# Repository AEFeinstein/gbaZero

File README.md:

View this project on [CADLAB.io](https://cadlab.io/project/1072). 

# gbaZero

One day I decided to buy a broken Gameboy Advance, gut it, and replace the innards with a Raspberry Pi powered board. This style of project has been attempted before in custom plastic (see [Game Grrl](https://learn.adafruit.com/game-grrl) and its derivitaves) and Nintendo plastic (see [Ryzee119's project](https://github.com/Ryzee119/GBA_Emulator-by-Ryzee119-) and [Game Pie Advance](http://gamepieadvance.com/)). Here's a little build log for my version of this project.

## Design

The design process was mostly me sitting at my desk doing research and CAD work in Inkscape and EAGLE.

To get the right PCB shape, I desoldered all the parts from a sacrificial PCB and took a 600dpi scan of it.

That scan was then traced in Inkscape, and the resulting SVG was imported into EAGLE using [cmonr's svg2poly ULP](https://github.com/cmonr/Eagle-ULPs).

I wanted the wacky button footprints to be just like Nintendo's. I had a scan of the footprints open in an image viewer, overlaid an EAGLE window made transparent by [Peek Through](http://www.lukepaynesoftware.com/projects/peek-through/), and traced out the shape using the polygon tool. It's kind of like a high tech lightbox.

Ultimately I threw my work on the board shape and drilled holes out the window in favor of the shape from Ryzee119's project. I was almost guaranteed to mess something, and their's was already tested to be the right fit, so that seemed safer. I was also unaware of Ryzee119's project when I started all the scanning and tracing. I did keep the Nintendo-esque button footprints.

## Assembling the Hardware

### Power Circuitry

It turns out using someone else's work is often easier than doing it yourself. In this case, I used a [PowerBoost 1000C](https://www.adafruit.com/products/2465) to manage charging the battery and supplying power for this board. It's a capable little board, so all I had to do was desolder the JST battery connector to trim the height and cover the backside with electrical tape because it will sit flush on the main board.

Here's the power circuit all soldered up. I'm using a common anode tricolor LED and some NOR gates and inverters to display the GBA's state (powered on, charging, or low battery). The logic ICs are in the top left and the LED is on the other side of the board.

The switch in the bottom right was salvaged from a broken GBA. I couldn't find where to source a replacement for the life of me. The resistor and diode in the bottom right are a way to have the Raspberry Pi power off cleanly. Sure, one could just cut power to the Pi, but that puts the SD card at risk for corruption. The Enable pin on the PowerBoost is tied to both the switch and a GPIO (through a diode, so the GPIO doesn't get backpowered), so when the Pi boots it holds the PowerBoost on, even if the switch is turned off. Flicking the switch off does trigger a shutdown script, which shuts down cleanly and disables the PowerBoost at the end.

Uhoh, notice those ugly wires coming off the logic ICs in the previous image? Turns out I either used the wrong footprint in EAGLE or ordered the wrong package part from Digi-Key. Either way, it needed some bridging. I realized I could take pictures with my phone through the stereo microscope in the lab, so I did. I trimmed the wires after this shot, and cleaned up the extra flux too.

There's nothing like a little hot glue to keep everything in place!

Ta-da! The LED works and is in the right place for the light pipe. It may be a little too bright, but that's nothing a larger current limiting resistor can't fix. The LED is blue when the unit is powered on, green when it is charging, and red when the battery is low. The one wrinkle is that the LED is off when the unit is off, but charging. The original design assumed a common cathode LED instead of a common anode LED, which is what I ended up finding on Digi-Key. Rather than redo the logic, I just threw an inverter on at the end. Unfortunately the inverter was powered by the regulated voltage, so it doesn't invert unless the unit is on. Had the LED been common cathode, it would have been driven by the 5V USB charging voltage. Ah well.

Also of note, the board uses the original Link Cable connector and a custom cable for charging. The Raspberry Pi's RX and TX pins are also exposed on the Link Cable connector, so with an FTDI cable one can log into a terminal and fiddle around with the system. This ended up being way more convenient than SSHing into the system over wifi.

### Display Circuitry

Remember that part about using someone else's work? I'll call it standing on the shoulders of giants. Turns out Adafruit sells a [2.8" Raspberry Pi display](https://www.adafruit.com/products/2423) which fits pretty perfectly in a GBA. I took the [circuitry from their board](https://github.com/adafruit/Adafruit-PiTFT-Plus-2.8-PCB) and transposed it onto mine. Should work perfectly, right? Yeah, we'll get to that.

Here's a gratuitious microscope shot. The display connector had 0.5mm pitch pins, which is the smallest thing I've soldered. Solder braid makes everything look super clean (and not bridged).

Oh yeah, I was going wild with that microscope. There's actually a problem in this picture. I'll get to that shortly.

Transposing a circuit only works if you do it correctly, which I did not. I crossed the I2C lines which send touchscreen data to the Raspberry Pi, so I had to cut those traces with a knife and reroute them with magnet wire. Those are the two wires going off the edge of the board. That didn't matter so much as I wasn't using the touchscreen anyway, but I like to be proper. The bigger issue is that I completely missed a trace that had been connected with a 0 ohm resistor on Adafruit's board. That was fixed with the third magnet wire running from the display connector to U1. I opted for kapton tape instead of hot glue to hold these fixes in place.

There was another issue with the display circuitry that prevented an image from being displayed, hinted at before. U1 is an APX803 voltage supervisor on a 3.3V line. However, I bought an APX803 which had a 4.63V threshold. D'oh. The Adafruit schematic didn't note the treshold level, and I must not have been paying much attention while filling my shopping cart. In lieu of ordering another supervisor, I stole the one from the Adafruit board and dropped it on mine.

Ta-da! With a few magnet wire fixes and a new supervisor, there's an image! This testing and debugging was done after all the parts were soldered, so these images aren't quite in chronological order. It would be hard to display anything without the Raspberry Pi.

### Audio Circuitry

While most Raspberry Pis have audio output, the Zero does not. It's the cost to pay for a tiny $5 board. Luckily, it can still output a PWM audio signal. A little RC filtering and amplifying later, and it should be good to go. The headphone jack and volume potentiometer were new parts. A minor annoyance, GND and 5V are swapped on the volume potentiometer, so rotating it towards max volume (according to the plastic shell) makes it quieter. 

Here's a microscope shot of the buffer and five passives that make up the filter. The design was taken from the Raspberry Pi 3 schematic. Once again, there's a problem in here. More on that shortly.

The amplifier is an LM4875. That amp only does mono sound, but it can automatically switch between a speaker and a headphone jack. An earlier design had a separate analog switch IC which could handle stereo output, but was way more cumbersome. The GBA only has one speaker anyway (though headphones have two).

So about that problem, when I went to test the audio, the speaker got hot. As a colleague said "you can't hear DC," and indeed there was an unexpected DC voltage across the speaker. The [Raspberry Pi 3 schematic](https://www.raspberrypi.org/documentation/hardware/raspberrypi/schematics/RPI-3B-V1_2-SCHEMATIC-REDUCED.pdf) I copied the audio circuitry from had a pulldown resistor right before the audio jack. This is great for headphones or speakers or what-have-you, but terrible for amplifier input. In fact, the [LM4875 datasheet](http://www.ti.com/lit/ds/symlink/lm4875.pdf) says to put a 0.22uF capacitor in line with the input signal to get rid of incoming DC voltage, which I did not do. All that had to change was to remove the last pulldown resistor before the amplifier and let the last capacitor filter out all the DC voltage. You can see R12 hanging off into nowhere, just so I wouldn't lose it.

This took me forever to figure out, and in fact the solution was proposed by a colleague who earned his name in the silkscreen for version two. Some failed debugging attempts were powering the audio circuitry with 3.3V instead of 5V (the cut and solder blob in the top left), replacing R13 with a wire, dis/reconnecting the volume potentiometer, and changing bypass capacitor values (C7 is two stacked capacitors in the picture above). Gross.

### Raspberry Pi Zero

Soldering on the Raspberry Pi proved to be the one part of this project that went as expected. First I soldered on a 40 pin SMD connector.

Then I taped the bottom of the Raspberry Pi, since it would cantilever over the PowerBoost.

Then I soldered it on the header. All good! This picture was taken after the display debugging, so you can see where those two magnet wires ended up. I also made a note to myself on the circuit board, seemed easier that way.

By now, the shoulder buttons had also been soldered on. I tried to use the original buttons to have a realistic feel. The buttons were tactile switch, but the plunger was made of a flexible rubber rather than a hard plastic. Unfortunately, one of the switches would not switch at all. I don't know what this poor Gameboy went through in a prior life, but it could not have been good. We had one 90 deggree tactile switch in the office, so I bent it's pins and jammed it on the board, which worked just fine. The shoulders currently have an asymetrical feel though, which kind of drives me nuts.

### It Lives!

At the end, everything get put in the salvaged plastic, and yes, it runs Doom! I popped off the old display lens because it was so roughed up and the Adafruit display can hold it's own.

### The Plastic

There are tons of Gameboy Advance shell replacement kits available on Amazon, so it seemed right to replace the scarred purple shell. I went with yellow because my first Gameboy, a Color, was yellow. Thanks Mom & Dad!

The plastic has all sorts of interior supports for the cartridge and battery, but those need to be removed here.

A dremel probably would have worked wonders here, but I opted to "cut" the plastic away with a soldering iron. Melted ABS fumes aren't pleasant (or healthy), so this work was done under a vacuum.

The battery compartment was a little trickier to remove partially because it was larger and partially because I had to remove material close to that bottom edge. I ended up applying a little too much heat and the bottom edge warped a bit. It's not bad enough to prevent the shell from fitting, but you can see it from the outside if you're looking for it. Plus I know it's there. Dang.

The display is held in place with the thinnest double sided foam tape I could find on Digi-Key. I finally removed the film protecting the screen before mounting, and boy does it look clearer. It's not easy to finagle the ribbon cable into the connector when the display is mounted, but it's doable.

And voila! The display lens has been installed and I'm done. What better way to celebrate than with the greatest first person shooter of all time, Chex Quest?

### PCB v2

I wasn't really happy with the IC pad size for the power LED logic, or the asymmetrical shoulder buttons, or the fix wires for the display, and I wanted to try out Seeed Studio's PCB Assembly service, so I recruited a few friends to defray the cost for a batch of 10 PCBs fixed the layout, and had them built. Seeed Studio couldn't assemble the whole board, but it was quite nice not having to solder everything. Here it is in all its glory.

But of course there was something still broken (hardware is hard). Even though the power LED's logic gates are still powered when the unit is off but charging, the LED itself is not. Nothing a wire couldn't fix. This one I'll have to live with.

I noticed some odd behaviour when trying to turn on and off the gbaZero v2 PCB as well. After a little investigation, it turns out that the original GBA power "switch" was actually a linear potentiometer. Seriously Nintendo? It kind of works as a switch, but not always, which is why I hadn't noticed until now. I'm not planning on a v3, so I scoured Digi-Key for a switch with the same footprint and [managed to find one](https://www.digikey.com/product-detail/en/nidec-copal-electronics/CSS-1310TB/563-1095-1-ND/1124228). The actuator dimensions were slightly off, so I had to 3D print a new piece. Works like a charm!

At the very end of the project, the Wind Fish is saved! I found that deeply satisfying.

## The Software

Software doesn't get pretty pictures, sorry.

I connected a USB wifi dongle to the Raspberry Pi using a USB OTG cable and configured with [these instructions](http://weworkweplay.com/play/automatically-connect-a-raspberry-pi-to-a-wifi-network/). I only used wifi during configuration.

The base OS is [Adafruit's version of Jessie Lite](https://learn.adafruit.com/adafruit-2-8-pitft-capacitive-touch/easy-install), with kernel drivers for the display already built in. [RetroPie](https://retropie.org.uk/) was installed on top of that, which handles all of the game playing. I also used [another of Adafruit's guides](https://learn.adafruit.com/running-opengl-based-games-and-emulators-on-adafruit-pitft-displays/pitft-setup) to install fbcp, necessary to draw to the display from RetroPie. 

[Retrogame](https://github.com/adafruit/Adafruit-Retrogame) was used to map the button GPIOs to actual key input. I had to further modify the mappings in Emulationstation (a part of RetroPie) because some games expected key combinations that happened to do other things, like quit the game.

[Wiring Pi](http://wiringpi.com/) was used to set and monitor the power switch GPIOs.

[These instructions](http://stackoverflow.com/questions/33753985/raspberry-pi-auto-login-without-etc-inittab/34755133#34755133) enabled auto-login, and [these instructions](https://www.raspberrypi.org/forums/viewtopic.php?f=78&t=58233) started Emulationstation automatically.

One hiccup was that initially there was no audio output, even though it was set to play over the "3.5mm jack" instead of HDMI. The solution? Unmute the audio. Occam's Razor hard at work.

The other hiccup was a hardware failure. Every once in a while, though with increasing frequency, the Raspberry Pi wouldn't boot, but would print "mmc0: fsm 1, hsts 1" to the terminal in an infinite loop. Turns out the SD card was busted and had to be replaced. Good thing I made a system image after tweaking the install to my liking.

## Final Thoughts
Hardware design is hard, and not everything can be fixed in software. Most of the janky fixes from the v1 PCB were fixed in the v2 one, but it's still not perfect. If only fabricating a board was as easy as typing "make." Also, Link's Awakening DX is still awesome.

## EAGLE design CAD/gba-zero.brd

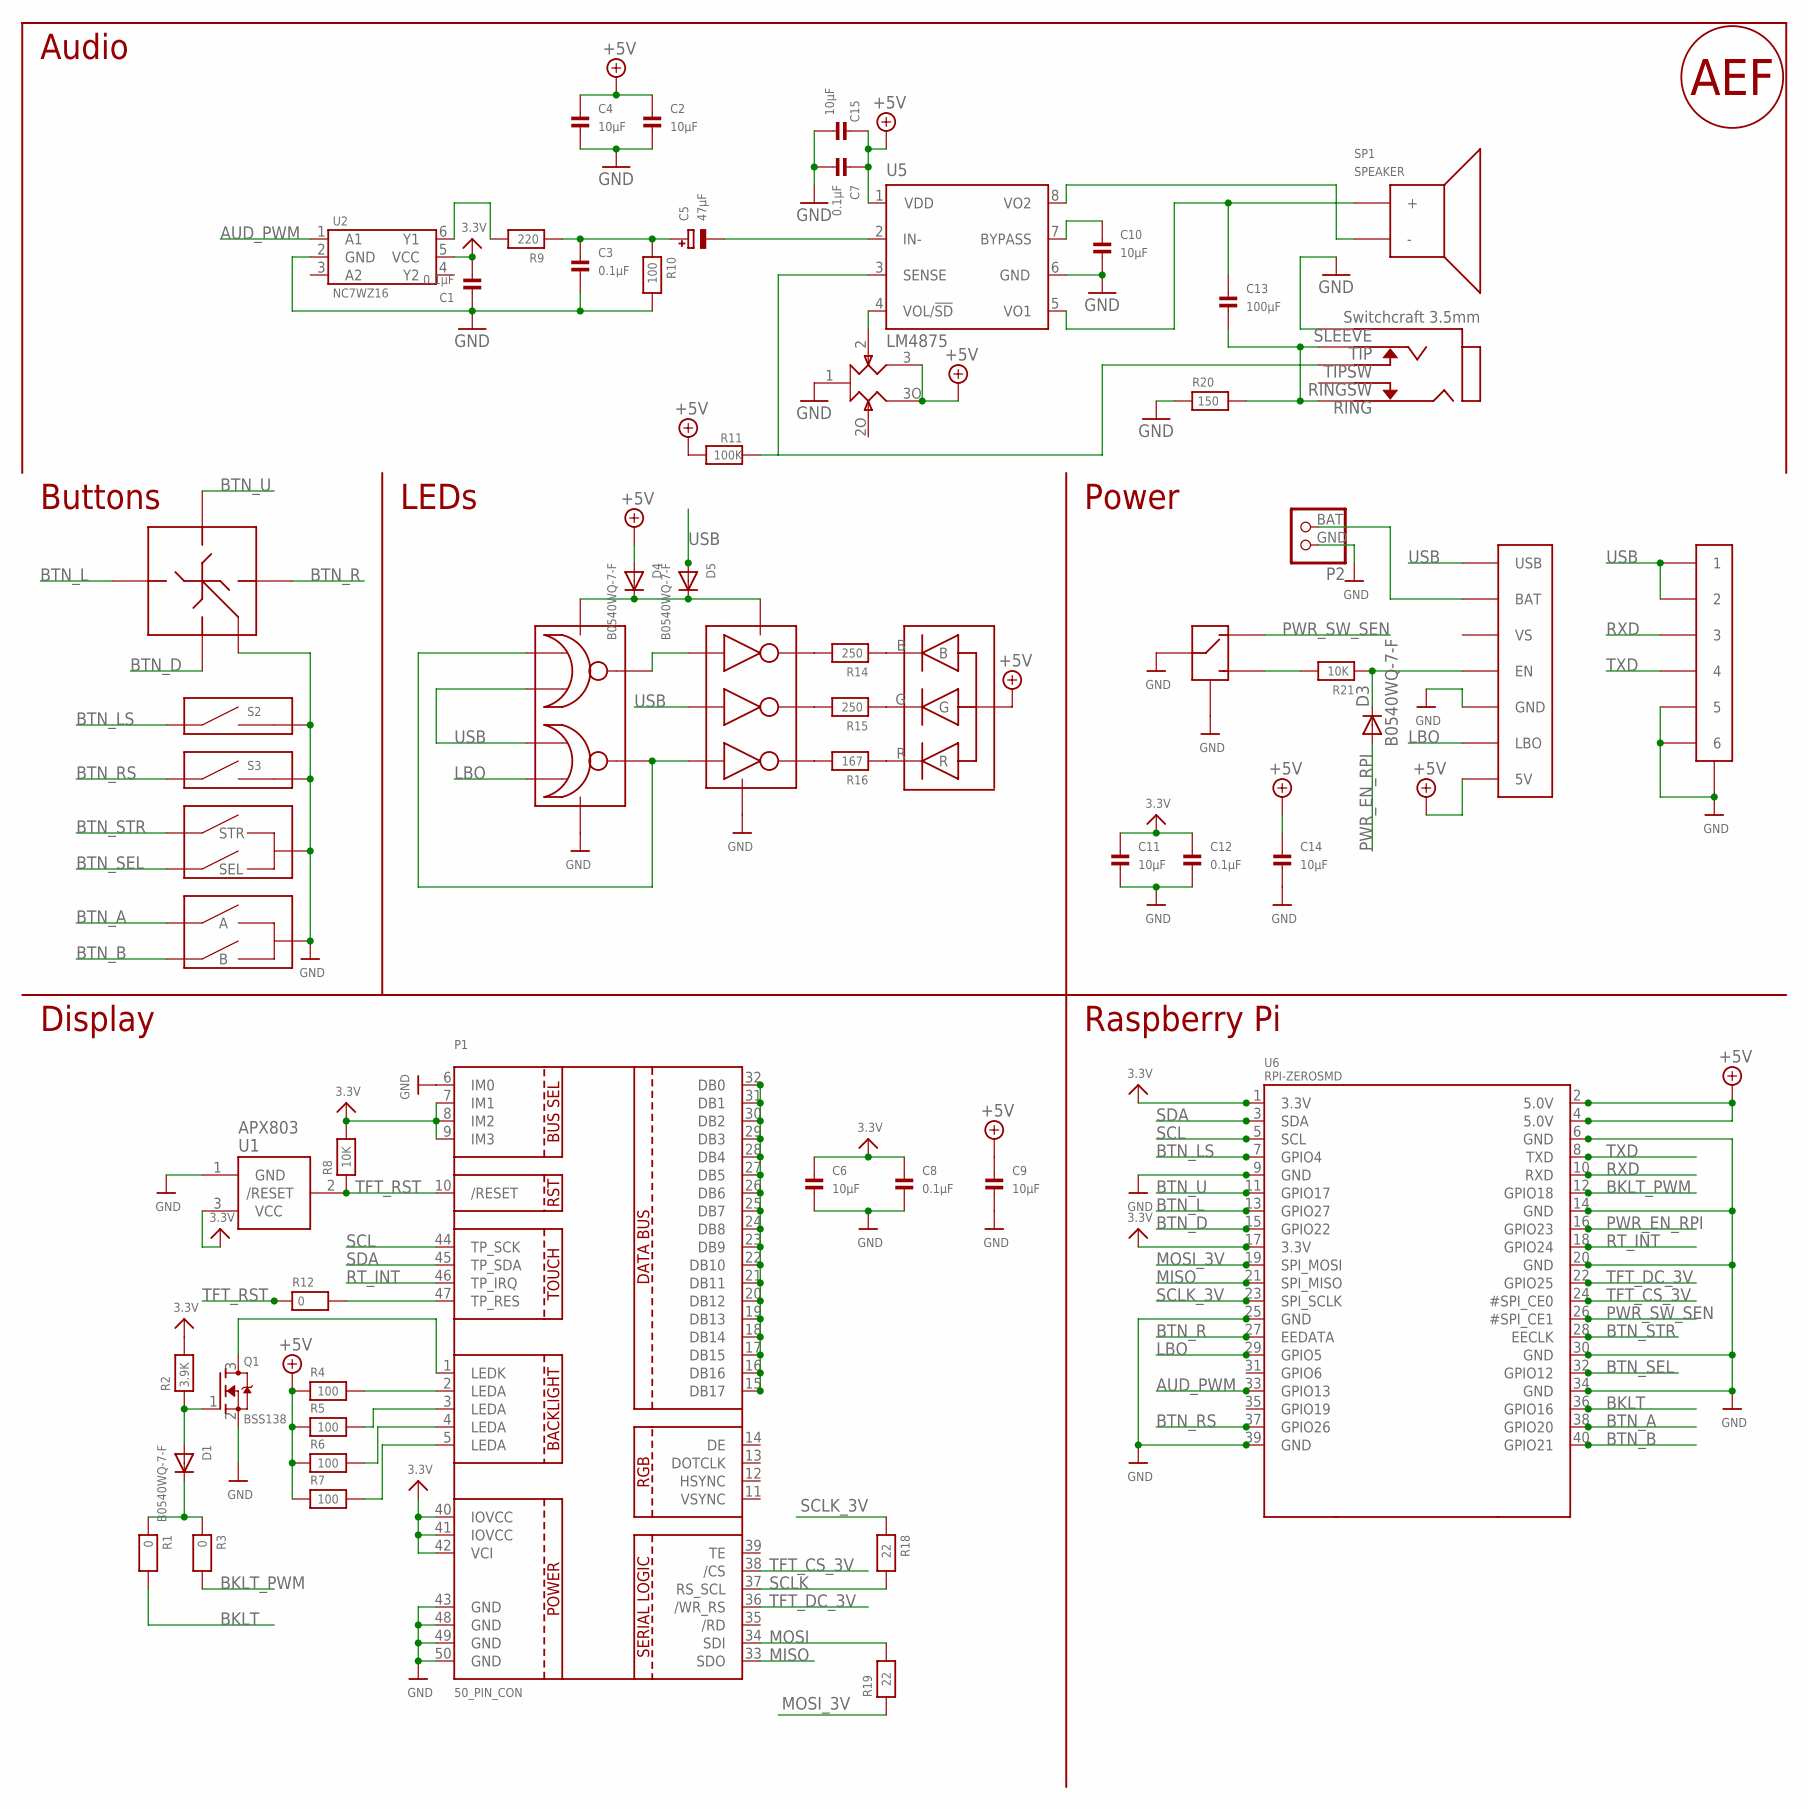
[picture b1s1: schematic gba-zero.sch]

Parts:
C1, C3, C7, C8, C12: 0.1μF; 0603
C2, C4, C6, C9, C10, C11, C14, C15: 10μF; 0603
C5: 47μF; EIA6032-28/C-R
C13: 100μF; 1206
D1, D3, D4, D5: B0540WQ-7-F; SOD-123
D2: LTST-C19HE1WT; WL-SBCW-0606
J1: SWTCHCRFT_3.5JACK5-JACK-SMD; 4-JACK-SMD
P1: 50_PIN_CON; FPC-50-CON
P2: JST_2PIN; JSTPH2
P3: LINK_CONNECTOR
Q1: BSS138; SOT23-WIDE
R1, R3, R12: 0; 0603
R2: 3.9K; 0603
R4, R5, R6, R7, R10: 100; 0603
R8, R21: 10K; 0603
R9: 220; 0603
R11: 100K; 0603
R14, R15: 250; 0603
R16: 167; 0603
R17: 10K; RK10J12E0A0A
R18, R19: 22; 0603
R20: 150; 0603
S1: D-PAD
S2, S3: SHOULDER_BUTTON
S4: START_SELECT_BUTTON
S5: AB_BUTTON
S6: PWR_SWITCH; PWR-SWITCH
SP1: SPEAKER
U1: APX803; SOT23
U2: NC7WZ16; SC-70-6
U3: 74LVC2G02; TSSOP-8
U4: 74LVC3G04; TSSOP-8
U5: LM4875; SO-8
U6: RPI-ZEROSMD; RPI-SMD
U7: POWERBOOST-1000C
U$1: SIGNATURE

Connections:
3.3V: C1.2, C6.1, C8.1, C11.1, C12.1, P1.7 (IM1), P1.8 (IM2), P1.9 (IM3), P1.40 (IOVCC), P1.41 (IOVCC), P1.42 (VCI), R2.2, R8.2, U1.3 (VCC), U2.5 (VCC), U6.1 (3.3V), U6.17 (3.3V)
+5V: C2.1, C4.1, C7.1, C9.1, C14.1, C15.1, D2.VCC, D4.A, R4.1, R5.1, R6.1, R7.1, R11.2, R17.3, R17.3O, U5.1 (VDD), U6.2 (5.0V), U6.4 (5.0V), U7.5V
AUD_PWM: U2.1 (A1), U6.33 (GPIO13)
BAT: P2.BAT (2), U7.BAT
BKLT: R1.2, U6.36 (GPIO16)
BKLT_PWM: R3.2, U6.12 (GPIO18)
BTN_A: S5.A@1 (A), S5.A@2 (A), U6.38 (GPIO20)
BTN_B: S5.B@1 (B), S5.B@2 (B), U6.40 (GPIO21)
BTN_D: S1.DOWN, U6.15 (GPIO22)
BTN_L: S1.LEFT, U6.13 (GPIO27)
BTN_LS: S2.SW (1), U6.7 (GPIO4)
BTN_R: S1.RIGHT, U6.27 (EEDATA)
BTN_RS: S3.SW (1), U6.37 (GPIO26)
BTN_SEL: S4.SEL, U6.32 (GPIO12)
BTN_STR: S4.STR, U6.28 (EECLK)
BTN_U: S1.UP, U6.11 (GPIO17)
BYPASS: C10.1, U5.7 (BYPASS)
GND: C1.1, C2.2, C3.2, C4.2, C6.2, C7.2, C8.2, C9.2, C10.2, C11.2, C12.2, C14.2, C15.2, J1.1, P1.6 (IM0), P1.43 (GND), P1.48 (GND), P1.49 (GND), P1.50 (GND), P2.GND (1), P3.5, P3.6, P3.GND@1 (GND), P3.GND@2 (GND), Q1.2 (S), R10.2, R17.1, R20.1, S1.GND@1 (GND), S1.GND@2 (GND), S1.GND@3 (GND), S1.GND@4 (GND), S2.GND@1 (2), S2.GND@2 (2), S2.GND@3 (2), S3.GND@1 (2), S3.GND@2 (2), S3.GND@3 (2), S4.GND@1 (GND), S4.GND@2 (GND), S4.GND@3 (GND), S4.GND@4 (GND), S5.GND@1 (GND), S5.GND@2 (GND), S5.GND@3 (GND), S5.GND@4 (GND), S6.C@1 (C), S6.C@2 (C), S6.GND@1 (GND), S6.GND@2 (GND), U1.1 (GND), U2.2 (GND), U3.4 (GND), U4.4 (GND), U5.6 (GND), U6.6 (GND), U6.9 (GND), U6.14 (GND), U6.20 (GND), U6.25 (GND), U6.30 (GND), U6.34 (GND), U6.39 (GND), U7.GND@1 (GND), U7.GND@2 (GND)
LBO: U3.6 (2B), U6.29 (GPIO5), U7.LBO
MISO: P1.33 (SDO), U6.21 (SPI_MISO)
MOSI: P1.34 (SDI), R19.2
MOSI_3V: R19.1, U6.19 (SPI_MOSI)
unnamed: P1.1 (LEDK), Q1.3 (D)
unnamed: P1.5 (LEDA), R7.2
unnamed: P1.4 (LEDA), R6.2
unnamed: P1.3 (LEDA), R5.2
unnamed: R16.2, U4.2 (3Y)
unnamed: D1.C, R1.1, R3.1
unnamed: D1.A, Q1.1 (G), R2.1
unnamed: D2.R, R16.1
unnamed: P1.15 (DB17), P1.16 (DB16), P1.17 (DB15), P1.18 (DB14), P1.19 (DB13), P1.20 (DB12), P1.21 (DB11), P1.22 (DB10), P1.23 (DB9), P1.24 (DB8), P1.25 (DB7), P1.26 (DB6), P1.27 (DB5), P1.28 (DB4), P1.29 (DB3), P1.30 (DB2), P1.31 (DB1), P1.32 (DB0)
unnamed: P1.2 (LEDA), R4.2
unnamed: R15.2, U4.5 (2Y)
unnamed: D2.G, R15.1
unnamed: R14.2, U4.7 (1Y)
unnamed: D2.B, R14.1
unnamed: U3.7 (1Y), U4.1 (1A)
unnamed: U3.1 (1A), U3.3 (2Y), U4.6 (3A)
unnamed: R21.2, S6.R
unnamed: D3.C, R21.1, U7.EN
unnamed: D4.C, D5.C, U3.8 (VCC), U4.8 (VCC)
unnamed: R9.2, U2.6 (Y1)
unnamed: C3.1, C5.+, R9.1, R10.1
unnamed: P1.47 (TP_RES), R12.2
unnamed: C5.-, U5.2 (IN-)
PWR_EN_RPI: D3.A, U6.16 (GPIO23)
PWR_SW_SEN: S6.L, U6.26 (#SPI_CE1)
RING: C13.2, J1.2, J1.3, R20.2
RT_INT: P1.46 (TP_IRQ), U6.18 (GPIO24)
RXD: P3.3, U6.10 (RXD)
SCL: P1.44 (TP_SCK), U6.5 (SCL)
SCLK: P1.37 (RS_SCL), R18.2
SCLK_3V: R18.1, U6.23 (SPI_SCLK)
SDA: P1.45 (TP_SDA), U6.3 (SDA)
SENSE: J1.5, R11.1, U5.3 (SENSE)
TFT_CS_3V: P1.38 (/CS), U6.24 (#SPI_CE0)
TFT_DC_3V: P1.36 (/WR_RS), U6.22 (GPIO25)
TFT_RST: P1.10 (/RESET), R8.1, R12.1, U1.2 (/RESET)
TXD: P3.4, U6.8 (TXD)
USB: D5.A, P3.1, P3.2, U3.2 (1B), U3.5 (2A), U4.3 (2A), U7.USB
VO1: C13.1, SP1.1 (+), U5.5 (VO1)
VO2: SP1.2 (-), U5.8 (VO2)
VOL/SD: R17.2, U5.4 (VOL/!SD)

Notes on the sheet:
Buttons
LEDs
Power
Raspberry Pi
Display
Audio

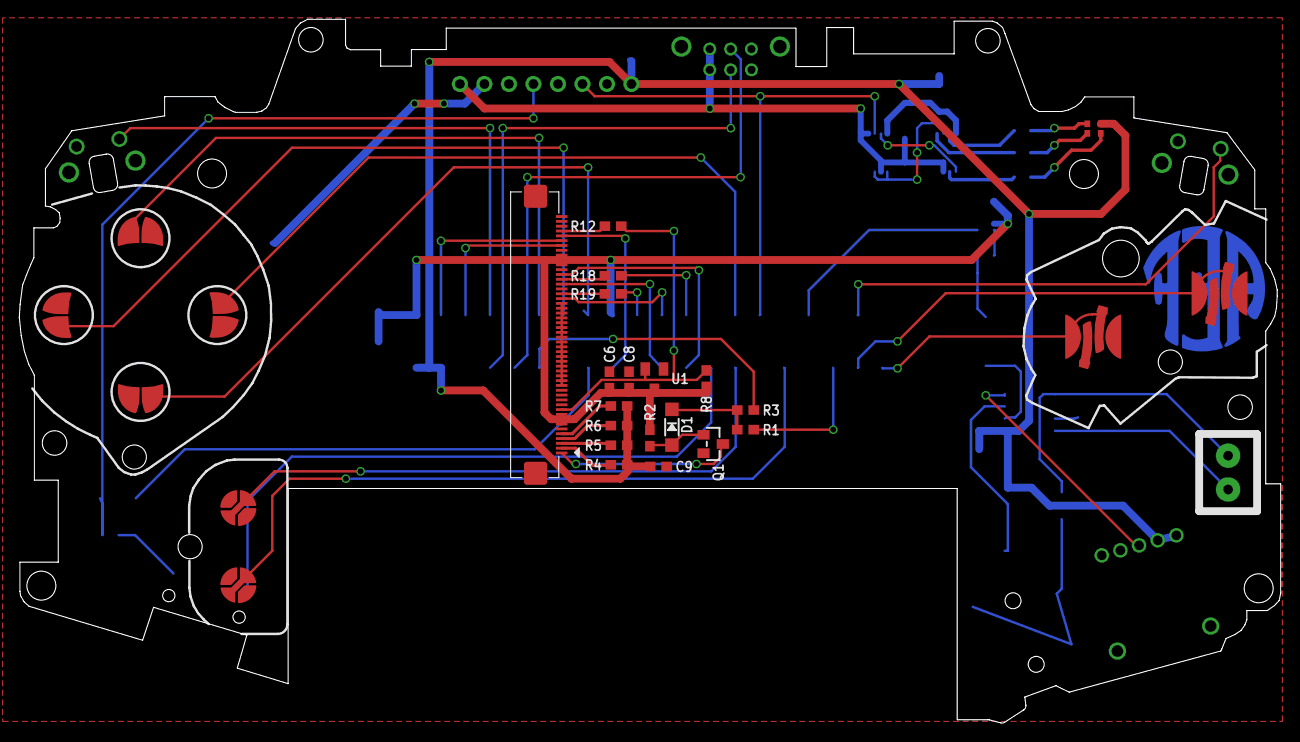
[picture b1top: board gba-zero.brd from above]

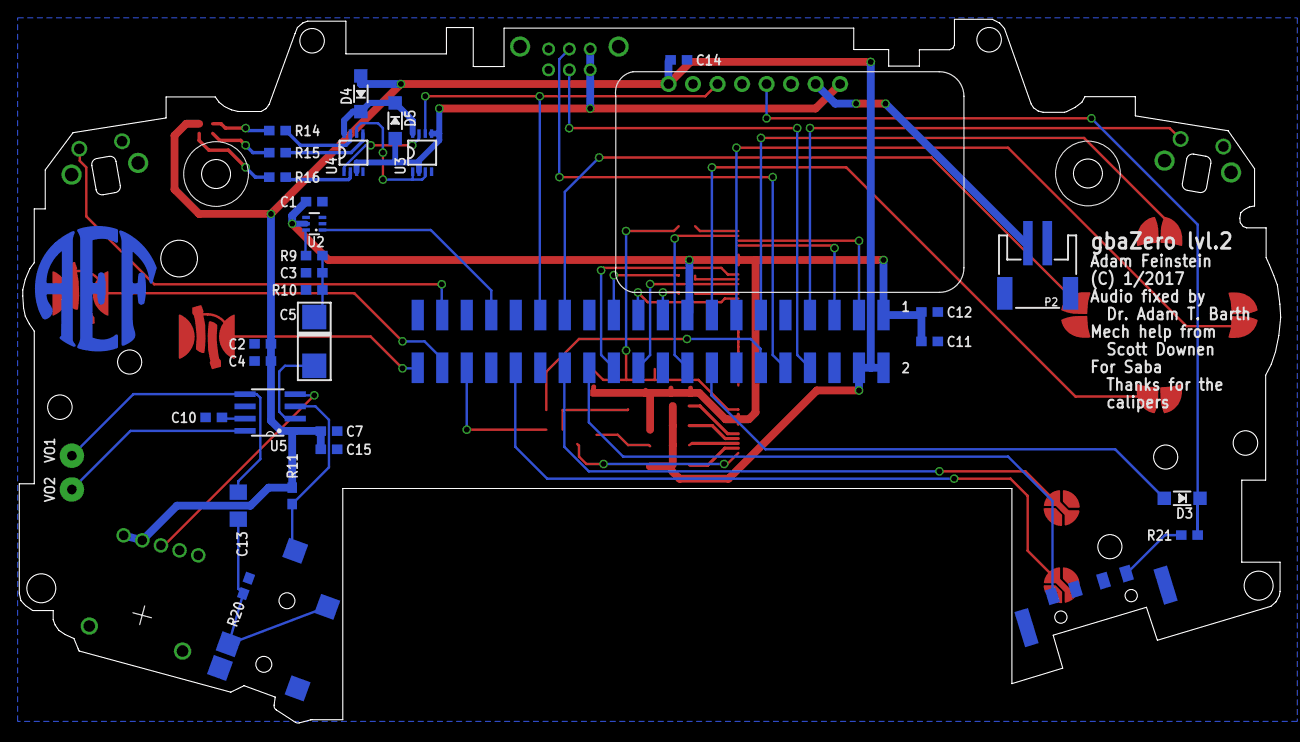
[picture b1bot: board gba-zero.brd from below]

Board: 2 copper layers, 130.7 x 72.9 mm, 60 parts (34 on the bottom side), 63 nets.

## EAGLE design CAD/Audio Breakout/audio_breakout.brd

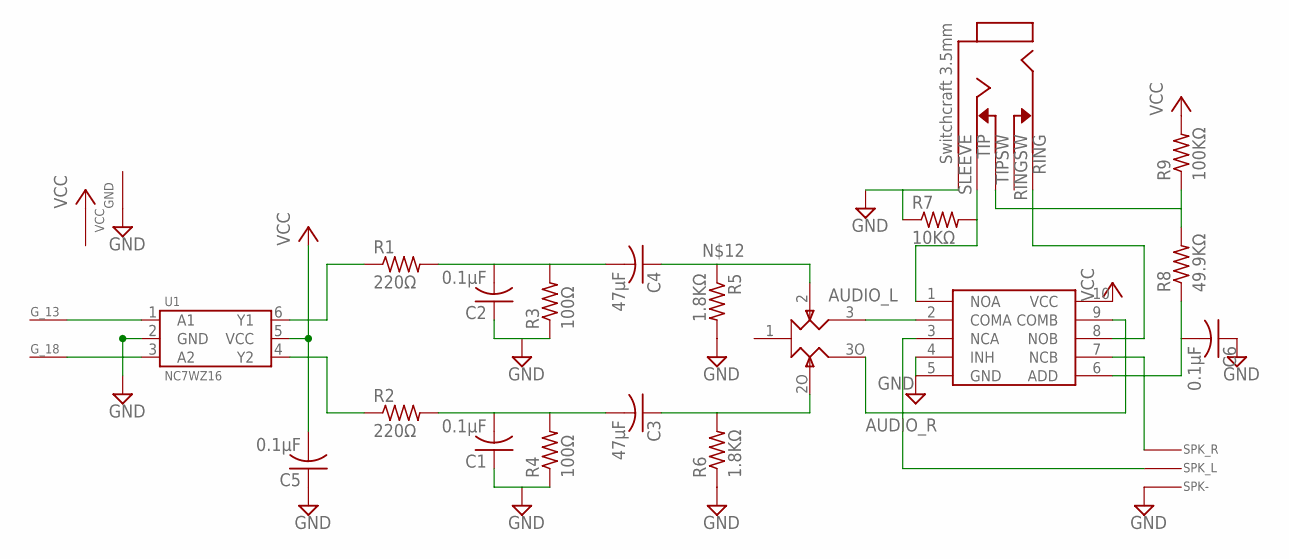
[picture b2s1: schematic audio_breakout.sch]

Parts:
C1, C2, C5, C6: 0.1μF; C0603
C3, C4: 47μF; C0603
GND: THROUGH-HOLE
G_13, G_18: THROUGH-HOLE
R1, R2: 220Ω; R0603
R3, R4: 100Ω; R0603
R5, R6: 1.8KΩ; R0603
R7: 10KΩ; R0603
R8: 49.9KΩ; R0603
R9: 100KΩ; R0603
SPK-: THROUGH-HOLE
SPK_L: THROUGH-HOLE
SPK_R: THROUGH-HOLE
U1: NC7WZ16; SC-70-6
U2: MAX4525L; UMAX10
U$2: SWTCHCRFT_3.5JACK5-JACK-SMD; 4-JACK-SMD
U$3: 10K; RK10J12E0A0A
VCC: THROUGH-HOLE

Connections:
AUDIO_L: U2.2 (COMA), U$3.3
AUDIO_R: U2.9 (COMB), U$3.3O
GND: C1.1, C2.1, C5.1, C6.1, GND.P$1, R3.1, R4.1, R5.2, R6.1, R7.1, SPK-.P$1, U1.2 (GND), U2.4 (INH), U2.5 (GND), U$2.1
unnamed: R1.1, U1.6 (Y1)
unnamed: R2.1, U1.4 (Y2)
unnamed: C1.2, C3.2, R2.2, R4.2
unnamed: C2.2, C4.2, R1.2, R3.2
unnamed: R8.2, R9.1, U$2.5
unnamed: C6.2, R8.1, U2.6 (ADD)
unnamed: G_18.P$1, U1.3 (A2)
unnamed: G_13.P$1, U1.1 (A1)
unnamed: SPK_R.P$1, U2.7 (NCB)
unnamed: R7.2, U2.1 (NOA), U$2.3
unnamed: U2.8 (NOB), U$2.2
unnamed: C4.1, R5.1, U$3.2
unnamed: SPK_L.P$1, U2.3 (NCA)
unnamed: C3.1, R6.2, U$3.2O
VCC: C5.2, R9.2, U1.5 (VCC), U2.10 (VCC), VCC.P$1

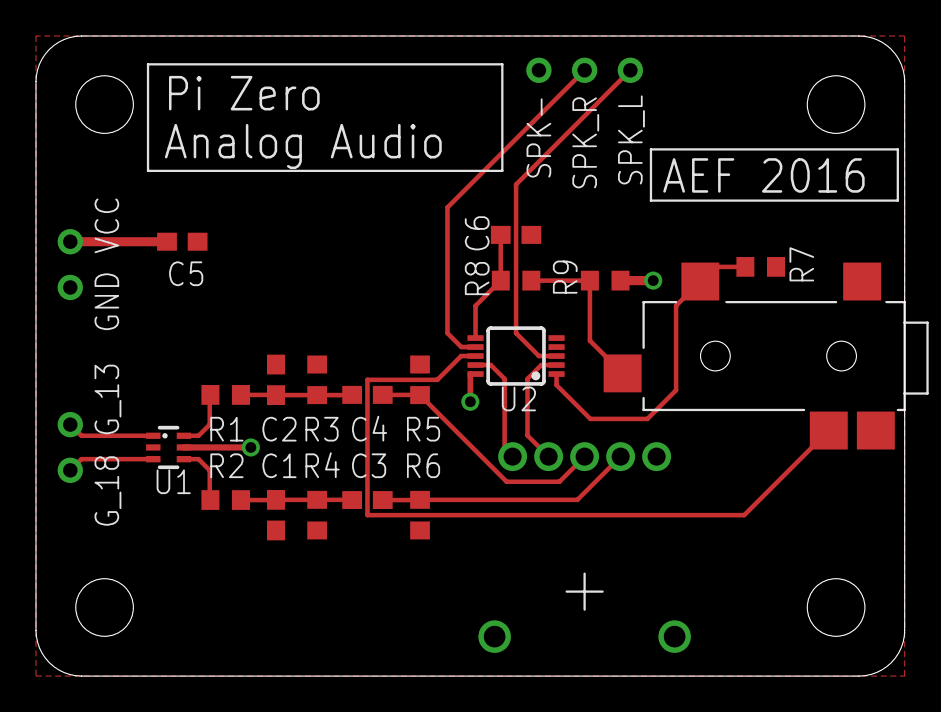
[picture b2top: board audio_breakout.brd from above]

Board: 2 copper layers, 48.3 x 35.6 mm, 26 parts (0 on the bottom side), 18 nets.

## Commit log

2016-11-23 Added SVG
2016-11-24 Did CAD work for D-Pad, Start & Select buttons
2016-11-25 Added link connector & shoulder button parts.
    TODO: verify electrical connections
2016-11-26 Parts & Schematic almost done, except AB buttons
2016-11-26 Added AB_BUTTON part to library & schematic
2016-11-28 Added audio to schematic
2016-11-28 Lots of schematic cleanup
2016-11-28 Added JST battery connector
2016-12-01 Added new parts for SMD RPI, just the 510 pin FPC connector Sorted parts in the layout
2016-12-01 Resized SVG to the proper dimension
2016-12-01 Scaled AB, STR/SEL, D-PAD to proper size
2016-12-01 Added Ryzee's parts for placement
2016-12-02 Started the layout. Tweaking parts as necessary
2016-12-03 Routed right side of the board
2016-12-04 More Routing
2016-12-04 Display is routed, some other stuff was unrouted
2016-12-05 Fully Routed
2016-12-05 Cleared all DRC errors
2016-12-05 Final board tweaks Added DRU file
2016-12-05 Switched DFRobot to SeeedStudio files
2016-12-05 Added value layers to the silkscreen
2016-12-05 Renumbered parts
2016-12-05 Fixed u vs. μ Removed jack outline from bPlace Fixed the date on the silk
2016-12-05 Added Gerber files
2016-12-06 Improved soldermask around d-pad and A&B buttons
2016-12-22 Added Audio Breakout files
2016-12-22 Added BOM, odds and ends images
2016-12-26 Rerouted display control lines Added missing connection between pins 10 & 47 on the display connector
2016-12-26 Shifted display hardware, added more space in the battery area
2016-12-26 Added diodes to power LED logic by USB & regulated 5V Cleaned up layout
2016-12-26 Added LBO to a GPIO5
2016-12-26 Moved RPi Zero up a little
2016-12-26 Updated APX803 to the right voltage on the BOM
2016-12-26 Replaced 0805s with 0603s Fattened power traces
2016-12-26 Fixed TSSOP-8 package
2016-12-26 Swapped VCC & GND for the volume dial
2016-12-26 Cleaned up the silkscreen
2016-12-27 Fixed drill sizes Smoothed out top edge
2016-12-27 Switched shoulder button footprint to one I can buy on digikey
2016-12-28 Updated BOM
2016-12-28 Updated BOM with quantity and part numbers
2016-12-29 Tweaked bypass capacitor values (C7, C10, C15) Removed unnecessary HP Sense resistor (R13) Removed pulldown resistor before amp (R12)
2016-12-29 Updated silkscreen Added 0 ohm to display connector for theoretical resistive compatibility Updated bom.ods
2016-12-30 Added signature
2016-12-30 Cleaned up traces because OCD
2016-12-30 Updated Gerbers
2016-12-31 Updated schematic, board, Gerbers, and BOM to use Seeed Studio PCBA parts where possible Updated CAM job to not silk t/bValue layers Shifted a drill hole just a little
2016-12-31 Added seeed-bom.csv
2016-12-31 Removed battery connector from seeed-bom.csv
2016-12-31 Updated silkscreen & gerbers
2017-01-02 Added images from the assembly process
2017-01-02 Create README.md
    With some images
2017-01-03 Added scaled PCB image
2017-01-04 Added images of plastic
2017-01-04 Updated final Assembly/28 - Final Assembly.jpg
2017-01-05 Expanded battery area in PCB Removed R1, R3 from seeed-bom.csv, since they are DNP Regenerated gerbers
2017-01-05 Fixed text orientation for speaker through holes
2017-01-05 Added gerber zips
2017-12-14 Added switch_mon program
2018-01-13 Updated README.md with v2 PCB info
2018-05-23 Backlink to CADLAB.io has been added.
2019-01-30 #1 Created LICENSE file, GPLv3

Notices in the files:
parts and their libraries:
SparkFun-Aesthetics: Licensing: Creative Commons ShareAlike 4.0 International - https://creativecommons.org/licenses/by-sa/4.0
